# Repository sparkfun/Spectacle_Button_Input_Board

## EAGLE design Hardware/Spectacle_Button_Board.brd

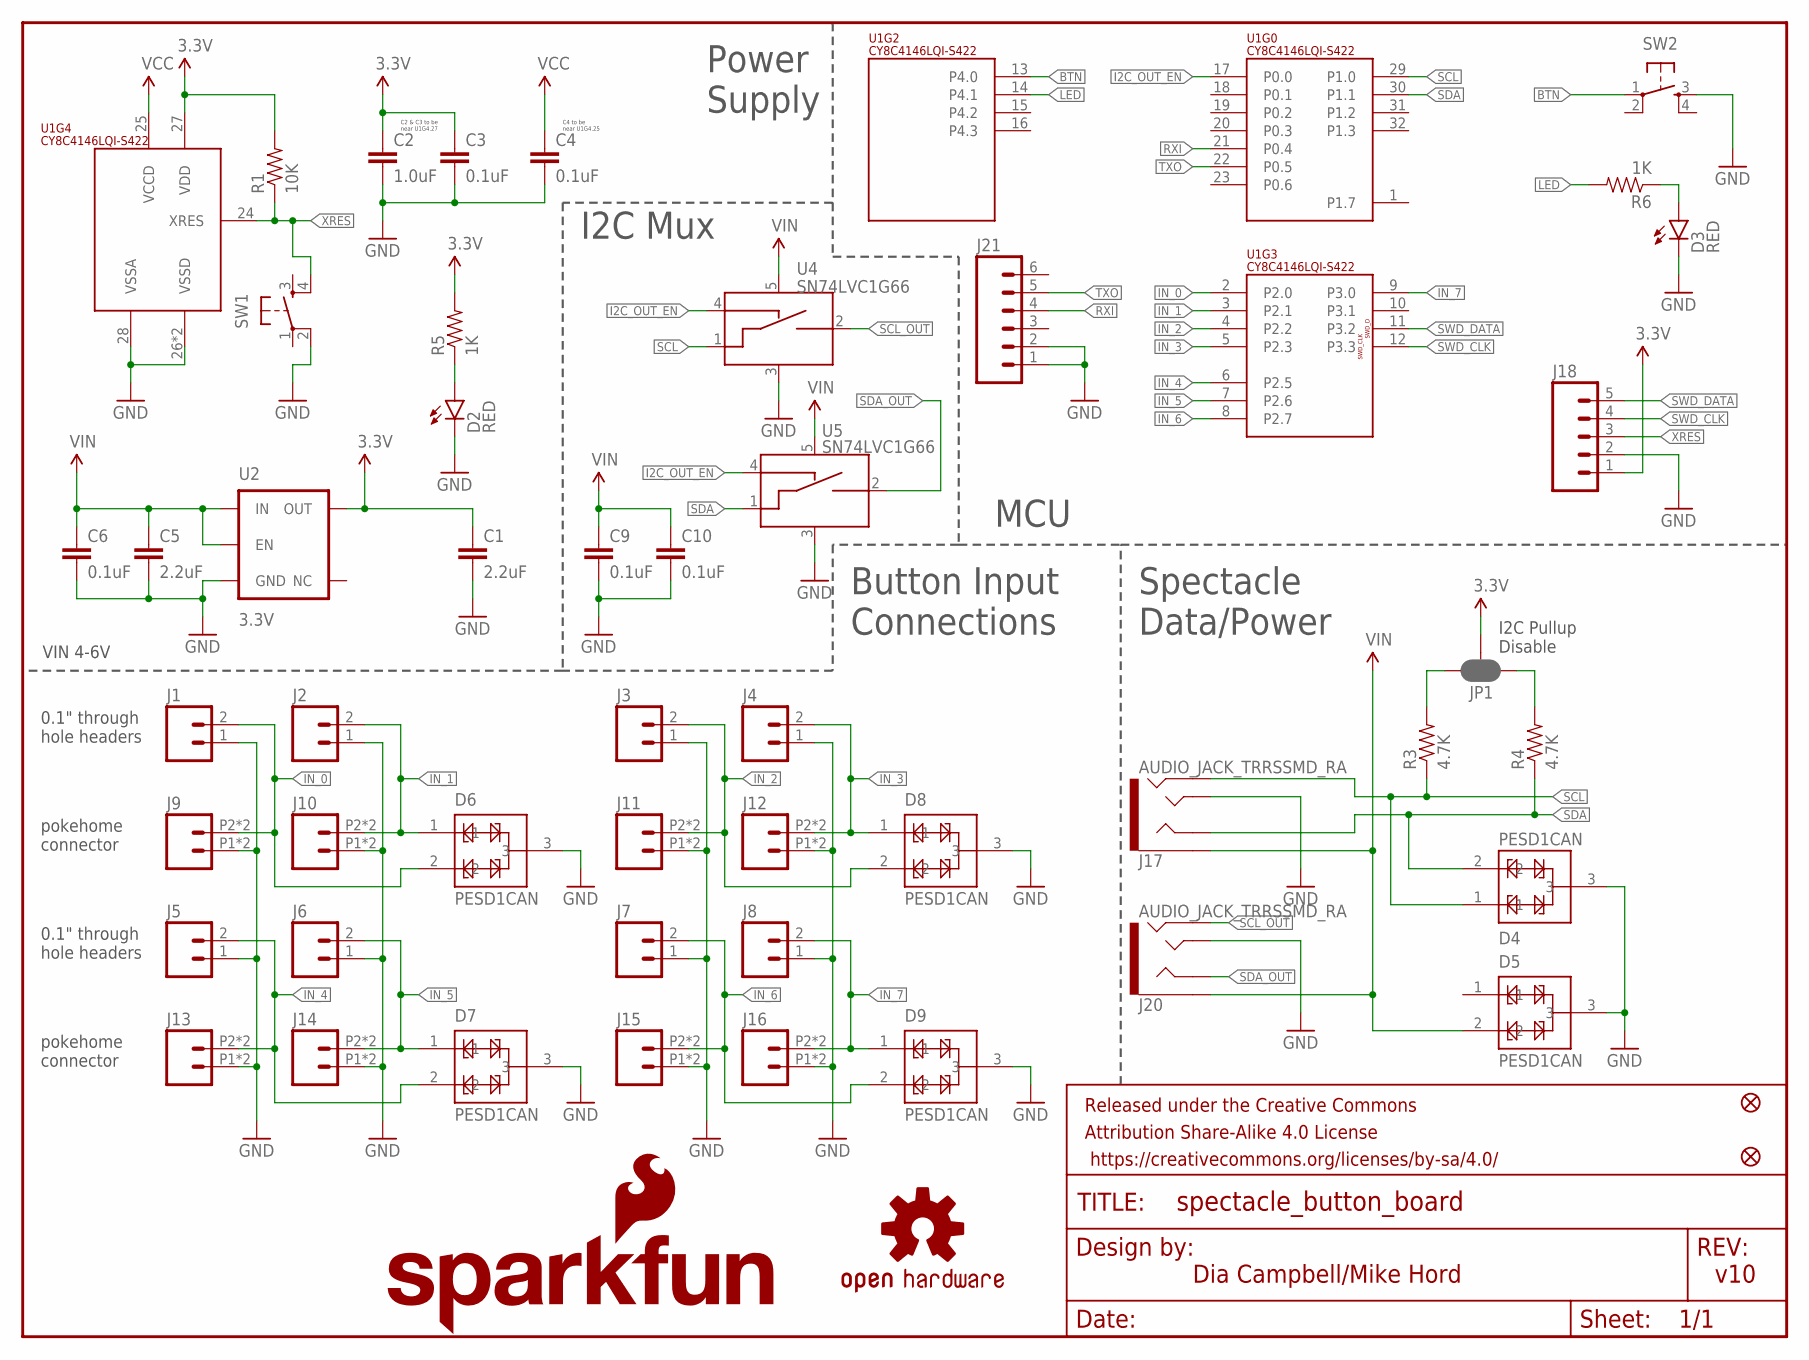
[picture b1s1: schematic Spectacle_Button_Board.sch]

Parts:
C1, C5: 2.2uF; 0603-CAP
C2: 1.0uF; 0402-CAP
C3, C4, C6, C9, C10: 0.1uF; 0402-CAP
D2, D3: RED; LED-0603
D4, D5, D6, D7, D8, D9: PESD1CAN; SOT23-3
FD1, FD2: FIDUCIALUFIDUCIAL; MICRO-FIDUCIAL
FRAME1: FRAME-LETTER; CREATIVE_COMMONS
J1, J2, J3, J4, J5, J6, J7, J8: M02PTH; 1X02
J9, J10, J11, J12, J13, J14, J15, J16: M02SMALL_POKEHOME; 1X02_POKEHOME
J17, J20: AUDIO_JACK_TRRSSMD_RA; AUDIO_JACK_3.5MM_TRRS_SMD_RA
J18: M05NO_SILK; 1X05_NO_SILK
J21: M06NO_SILK_NO_POP; 1X06_NO_SILK
JP1: JUMPER-PAD-3-NC_BY_PASTE; PAD-JUMPER-3-NC_BY_PASTE_YES_SILK_FULL_BOX
LOGO1: OSHW-LOGOM; OSHW-LOGO-M
LOGO2: SFE_LOGO_NAME_FLAME.1_INCH; SFE_LOGO_NAME_FLAME_.1
R1: 10K; 0603-RES
R3, R4: 4.7K; 0603-RES
R5, R6: 1K; 0603-RES
SW1, SW2: SWITCH_SPST_4_PINRECT; TACTILE_SWITCH_SMD_4.6X2.8MM
U1: CY8C4146LQI-S422; QFN-32
U2: 3.3V; SOT23-5
U4, U5: SN74LVC1G66; SOT23-5

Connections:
3.3V: C1.1, C2.1, C3.1, J18.1, JP1.2, R1.2, R5.2, U1.27 (VDD), U2.5 (OUT)
BTN: SW2.1, U1.13 (P4.0)
GND: C1.2, C2.2, C3.2, C4.2, C5.2, C6.2, C9.2, C10.2, D2.C, D3.C, D4.3, D5.3, D6.3, D7.3, D8.3, D9.3, J1.1, J2.1, J3.1, J4.1, J5.1, J6.1, J7.1, J8.1, J9.P1 (1), J9.P3 (1), J10.P1 (1), J10.P3 (1), J11.P1 (1), J11.P3 (1), J12.P1 (1), J12.P3 (1), J13.P1 (1), J13.P3 (1), J14.P1 (1), J14.P3 (1), J15.P1 (1), J15.P3 (1), J16.P1 (1), J16.P3 (1), J17.TIP, J18.2, J20.TIP, J21.1, J21.2, SW1.2, SW2.3, U1.26 (VSSD), U1.28 (VSSA), U1.EP (VSSD), U2.2 (GND), U4.3 (VSS), U5.3 (VSS)
I2C_OUT_EN: U1.17 (P0.0), U4.4 (CTRL_IN), U5.4 (CTRL_IN)
IN_0: D6.2, J1.2, J9.P2 (2), J9.P4 (2), U1.2 (P2.0)
IN_1: D6.1, J2.2, J10.P2 (2), J10.P4 (2), U1.3 (P2.1)
IN_2: D8.2, J3.2, J11.P2 (2), J11.P4 (2), U1.4 (P2.2)
IN_3: D8.1, J4.2, J12.P2 (2), J12.P4 (2), U1.5 (P2.3)
IN_4: D7.2, J5.2, J13.P2 (2), J13.P4 (2), U1.6 (P2.5)
IN_5: D7.1, J6.2, J14.P2 (2), J14.P4 (2), U1.7 (P2.6)
IN_6: D9.2, J7.2, J15.P2 (2), J15.P4 (2), U1.8 (P2.7)
IN_7: D9.1, J8.2, J16.P2 (2), J16.P4 (2), U1.9 (P3.0)
LED: R6.2, U1.14 (P4.1)
unnamed: JP1.3, R3.2
unnamed: D2.A, R5.1
unnamed: D3.A, R6.1
unnamed: JP1.1, R4.2
RXI: J21.4, U1.21 (P0.4)
SCL: D4.1, J17.RING2, R3.1, U1.29 (P1.0), U4.1 (A_IN)
SCL_OUT: J20.RING2, U4.2 (A_OUT)
SDA: D4.2, J17.RING1, R4.1, U1.30 (P1.1), U5.1 (A_IN)
SDA_OUT: J20.RING1, U5.2 (A_OUT)
SWD_CLK: J18.4, U1.12 (P3.3)
SWD_DATA: J18.5, U1.11 (P3.2)
TXO: J21.5, U1.22 (P0.5)
VCC: C4.1, U1.25 (VCCD)
VIN: C5.1, C6.1, C9.1, C10.1, D5.2, J17.EARTH, J20.EARTH, U2.1 (IN), U2.3 (EN), U4.5 (VCC), U5.5 (VCC)
XRES: J18.3, R1.1, SW1.4, U1.24 (XRES)

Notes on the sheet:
pokehome connector
0.1" through hole headers
C2 & C3 to be near U1G4.27
C4 to be near U1G4.25
Button Input Connections
Spectacle Data/Power
MCU
Power Supply
Dia Campbell/Mike Hord
v10
VIN 4-6V
I2C Mux
I2C Pullup Disable

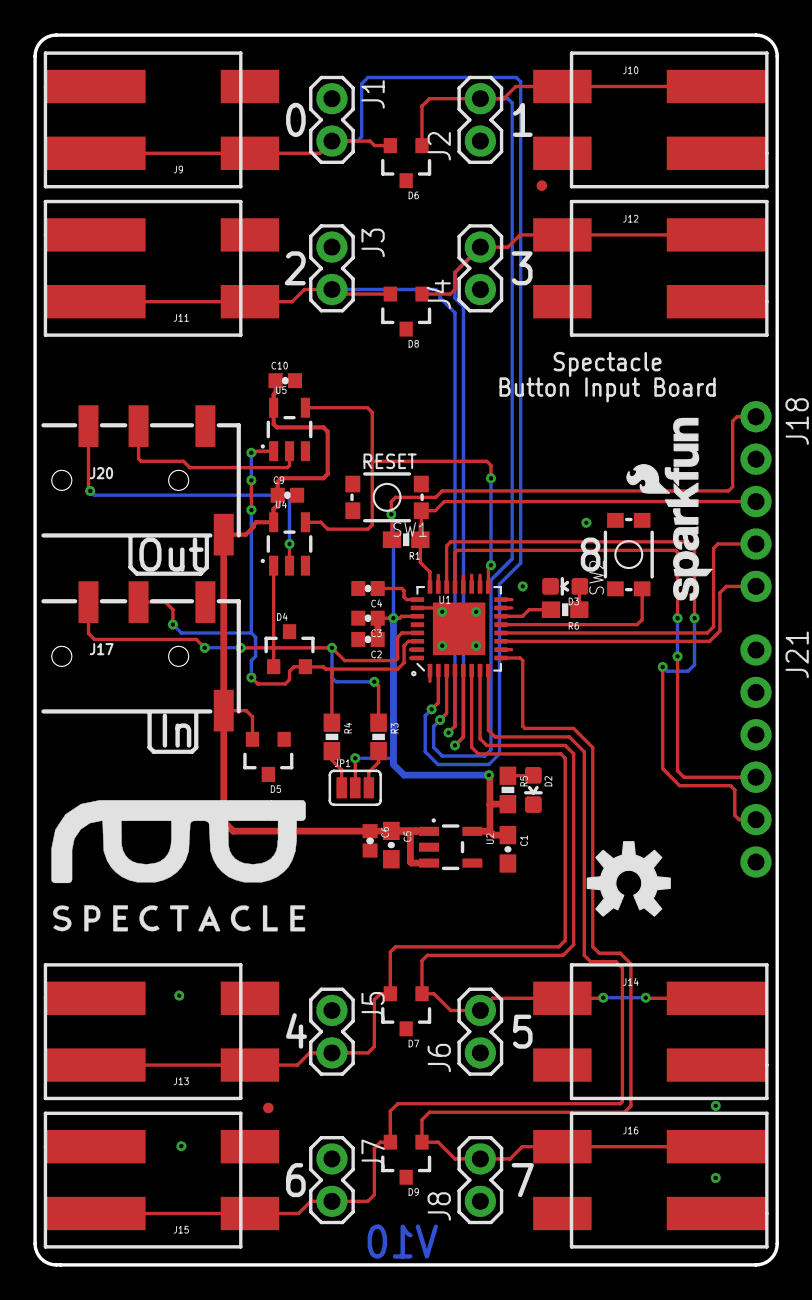
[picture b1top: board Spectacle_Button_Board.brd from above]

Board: 2 copper layers, 44.5 x 73.7 mm, 53 parts (0 on the bottom side), 28 nets.

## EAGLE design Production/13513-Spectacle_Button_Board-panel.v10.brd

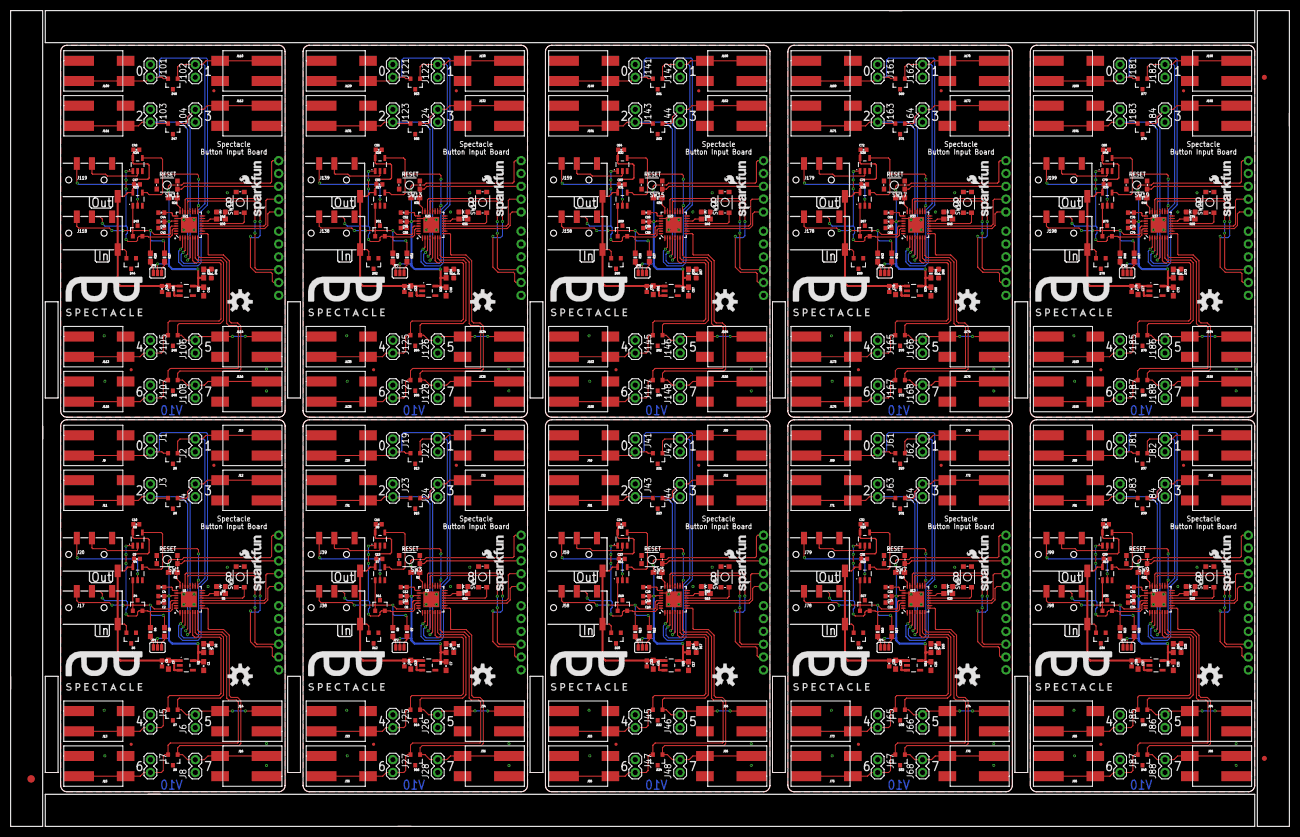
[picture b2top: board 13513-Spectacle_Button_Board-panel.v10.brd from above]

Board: 2 copper layers, 253.2 x 161.5 mm, 523 parts (0 on the bottom side), 280 nets.

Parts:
C1, C5, C7, C13, C17, C21, C25, C29, C33, C37, C41, C45, C49, C53, C57, C61, C65, C69, C73, C77: 2.2uF; 0603-CAP
C2, C8, C18, C26, C34, C42, C50, C58, C66, C74: 1.0uF; 0402-CAP
C3, C4, C6, C9, C10, C11, C12, C14, C15, C16, C19, C20, C22, C23, C24, C27, C28, C30, C31, C32, C35, C36, C38, C39, C40, C43, C44, C46, C47, C48, C51, C52, C54, C55, C56, C59, C60, C62, C63, C64, C67, C68, C70, C71, C72, C75, C76, C78, C79, C80: 0.1uF; 0402-CAP
D1, D2, D3, D10, D17, D18, D25, D26, D33, D34, D41, D42, D49, D50, D57, D58, D65, D66, D73, D74: RED; LED-0603
D4, D5, D6, D7, D8, D9, D11, D12, D13, D14, D15, D16, D19, D20, D21, D22, D23, D24, D27, D28, D29, D30, D31, D32, D35, D36, D37, D38, D39, D40, D43, D44, D45, D46, D47, D48, D51, D52, D53, D54, D55, D56, D59, D60, D61, D62, D63, D64, D67, D68, D69, D70, D71, D72, D75, D76, D77, D78, D79, D80: PESD1CAN; SOT23-3
E$1: FIDUCIAL-1.5X3
E$7, E$8: FIDUCIAL-1X2
FD1, FD2, FD3, FD4, FD5, FD6, FD7, FD8, FD9, FD10, FD11, FD12, FD13, FD14, FD15, FD16, FD17, FD18, FD19, FD20: FIDUCIALUFIDUCIAL; MICRO-FIDUCIAL
J1, J2, J3, J4, J5, J6, J7, J8, J19, J22, J23, J24, J25, J26, J27, J28, J41, J42, J43, J44, J45, J46, J47, J48, J61, J62, J63, J64, J65, J66, J67, J68, J81, J82, J83, J84, J85, J86, J87, J88, J101, J102, J103, J104, J105, J106, J107, J108, J121, J122, J123, J124, J125, J126, J127, J128, J141, J142, J143, J144, J145, J146, J147, J148, J161, J162, J163, J164, J165, J166, J167, J168, J181, J182, J183, J184, J185, J186, J187, J188: 1X02
J9, J10, J11, J12, J13, J14, J15, J16, J29, J30, J31, J32, J33, J34, J35, J36, J49, J50, J51, J52, J53, J54, J55, J56, J69, J70, J71, J72, J73, J74, J75, J76, J89, J90, J91, J92, J93, J94, J95, J96, J109, J110, J111, J112, J113, J114, J115, J116, J129, J130, J131, J132, J133, J134, J135, J136, J149, J150, J151, J152, J153, J154, J155, J156, J169, J170, J171, J172, J173, J174, J175, J176, J189, J190, J191, J192, J193, J194, J195, J196: 1X02_POKEHOME
J17, J20, J38, J39, J58, J59, J78, J79, J98, J99, J118, J119, J138, J139, J158, J159, J178, J179, J198, J199: AUDIO_JACK_TRRSSMD_RA; AUDIO_JACK_3.5MM_TRRS_SMD_RA
J18, J37, J57, J77, J97, J117, J137, J157, J177, J197: 1X05_NO_SILK
J21, J40, J60, J80, J100, J120, J140, J160, J180, J200: 1X06_NO_SILK
JP1, JP2, JP3, JP4, JP5, JP6, JP7, JP8, JP9, JP10: JUMPER-PAD-3-NC_BY_PASTE; PAD-JUMPER-3-NC_BY_PASTE_YES_SILK_FULL_BOX
LOGO1, LOGO3, LOGO5, LOGO7, LOGO9, LOGO11, LOGO13, LOGO15, LOGO17, LOGO19: OSHW-LOGOM; OSHW-LOGO-M
LOGO2, LOGO4, LOGO6, LOGO8, LOGO10, LOGO12, LOGO14, LOGO16, LOGO18, LOGO20: SFE_LOGO_NAME_FLAME.1_INCH; SFE_LOGO_NAME_FLAME_.1
R1, R2, R11, R16, R21, R26, R31, R36, R41, R46: 10K; 0603-RES
R3, R4, R7, R8, R12, R13, R17, R18, R22, R23, R27, R28, R32, R33, R37, R38, R42, R43, R47, R48: 4.7K; 0603-RES
R5, R6, R9, R10, R14, R15, R19, R20, R24, R25, R29, R30, R34, R35, R39, R40, R44, R45, R49, R50: 1K; 0603-RES
SW1, SW2, SW3, SW4, SW5, SW6, SW7, SW8, SW9, SW10, SW11, SW12, SW13, SW14, SW15, SW16, SW17, SW18, SW19, SW20: TACTILE_SWITCH_SMD_4.6X2.8MM
U1, U3, U9, U13, U17, U21, U25, U29, U33, U37: CY8C4146LQI-S422; QFN-32
U2, U6, U10, U14, U18, U22, U26, U30, U34, U38: 3.3V; SOT23-5
U4, U5, U7, U8, U11, U12, U15, U16, U19, U20, U23, U24, U27, U28, U31, U32, U35, U36, U39, U40: SN74LVC1G66; SOT23-5

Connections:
3.3V: C1.1, C2.1, C3.1, J18.1, JP1.2, R1.2, R5.2, U1.27, U2.5
3.3V1: C7.1, C8.1, C11.1, J37.1, JP2.2, R2.2, R9.2, U3.27, U6.5
3.3V2: C17.1, C18.1, C19.1, J57.1, JP3.2, R11.2, R14.2, U9.27, U10.5
3.3V3: C25.1, C26.1, C27.1, J77.1, JP4.2, R16.2, R19.2, U13.27, U14.5
3.3V4: C33.1, C34.1, C35.1, J97.1, JP5.2, R21.2, R24.2, U17.27, U18.5
3.3V5: C41.1, C42.1, C43.1, J117.1, JP6.2, R26.2, R29.2, U21.27, U22.5
3.3V6: C49.1, C50.1, C51.1, J137.1, JP7.2, R31.2, R34.2, U25.27, U26.5
3.3V7: C57.1, C58.1, C59.1, J157.1, JP8.2, R36.2, R39.2, U29.27, U30.5
3.3V8: C65.1, C66.1, C67.1, J177.1, JP9.2, R41.2, R44.2, U33.27, U34.5
3.3V9: C73.1, C74.1, C75.1, J197.1, JP10.2, R46.2, R49.2, U37.27, U38.5
BTN: SW2.1, U1.13
BTN1: SW4.1, U3.13
BTN2: SW6.1, U9.13
BTN3: SW8.1, U13.13
BTN4: SW10.1, U17.13
BTN5: SW12.1, U21.13
BTN6: SW14.1, U25.13
BTN7: SW16.1, U29.13
BTN8: SW18.1, U33.13
BTN9: SW20.1, U37.13
GND: C1.2, C2.2, C3.2, C4.2, C5.2, C6.2, C9.2, C10.2, D2.C, D3.C, D4.3, D5.3, D6.3, D7.3, D8.3, D9.3, J1.1, J2.1, J3.1, J4.1, J5.1, J6.1, J7.1, J8.1, J9.P1, J9.P3, J10.P1, J10.P3, J11.P1, J11.P3, J12.P1, J12.P3, J13.P1, J13.P3, J14.P1, J14.P3, J15.P1, J15.P3, J16.P1, J16.P3, J17.TIP, J18.2, J20.TIP, J21.1, J21.2, SW1.2, SW2.3, U1.26, U1.28, U1.EP, U2.2, U4.3, U5.3
GND1: C7.2, C8.2, C11.2, C12.2, C13.2, C14.2, C15.2, C16.2, D1.C, D10.C, D11.3, D12.3, D13.3, D14.3, D15.3, D16.3, J19.1, J22.1, J23.1, J24.1, J25.1, J26.1, J27.1, J28.1, J29.P1, J29.P3, J30.P1, J30.P3, J31.P1, J31.P3, J32.P1, J32.P3, J33.P1, J33.P3, J34.P1, J34.P3, J35.P1, J35.P3, J36.P1, J36.P3, J37.2, J38.TIP, J39.TIP, J40.1, J40.2, SW3.2, SW4.3, U3.26, U3.28, U3.EP, U6.2, U7.3, U8.3
GND2: C17.2, C18.2, C19.2, C20.2, C21.2, C22.2, C23.2, C24.2, D17.C, D18.C, D19.3, D20.3, D21.3, D22.3, D23.3, D24.3, J41.1, J42.1, J43.1, J44.1, J45.1, J46.1, J47.1, J48.1, J49.P1, J49.P3, J50.P1, J50.P3, J51.P1, J51.P3, J52.P1, J52.P3, J53.P1, J53.P3, J54.P1, J54.P3, J55.P1, J55.P3, J56.P1, J56.P3, J57.2, J58.TIP, J59.TIP, J60.1, J60.2, SW5.2, SW6.3, U9.26, U9.28, U9.EP, U10.2, U11.3, U12.3
GND3: C25.2, C26.2, C27.2, C28.2, C29.2, C30.2, C31.2, C32.2, D25.C, D26.C, D27.3, D28.3, D29.3, D30.3, D31.3, D32.3, J61.1, J62.1, J63.1, J64.1, J65.1, J66.1, J67.1, J68.1, J69.P1, J69.P3, J70.P1, J70.P3, J71.P1, J71.P3, J72.P1, J72.P3, J73.P1, J73.P3, J74.P1, J74.P3, J75.P1, J75.P3, J76.P1, J76.P3, J77.2, J78.TIP, J79.TIP, J80.1, J80.2, SW7.2, SW8.3, U13.26, U13.28, U13.EP, U14.2, U15.3, U16.3
GND4: C33.2, C34.2, C35.2, C36.2, C37.2, C38.2, C39.2, C40.2, D33.C, D34.C, D35.3, D36.3, D37.3, D38.3, D39.3, D40.3, J81.1, J82.1, J83.1, J84.1, J85.1, J86.1, J87.1, J88.1, J89.P1, J89.P3, J90.P1, J90.P3, J91.P1, J91.P3, J92.P1, J92.P3, J93.P1, J93.P3, J94.P1, J94.P3, J95.P1, J95.P3, J96.P1, J96.P3, J97.2, J98.TIP, J99.TIP, J100.1, J100.2, SW9.2, SW10.3, U17.26, U17.28, U17.EP, U18.2, U19.3, U20.3
GND5: C41.2, C42.2, C43.2, C44.2, C45.2, C46.2, C47.2, C48.2, D41.C, D42.C, D43.3, D44.3, D45.3, D46.3, D47.3, D48.3, J101.1, J102.1, J103.1, J104.1, J105.1, J106.1, J107.1, J108.1, J109.P1, J109.P3, J110.P1, J110.P3, J111.P1, J111.P3, J112.P1, J112.P3, J113.P1, J113.P3, J114.P1, J114.P3, J115.P1, J115.P3, J116.P1, J116.P3, J117.2, J118.TIP, J119.TIP, J120.1, J120.2, SW11.2, SW12.3, U21.26, U21.28, U21.EP, U22.2, U23.3, U24.3
GND6: C49.2, C50.2, C51.2, C52.2, C53.2, C54.2, C55.2, C56.2, D49.C, D50.C, D51.3, D52.3, D53.3, D54.3, D55.3, D56.3, J121.1, J122.1, J123.1, J124.1, J125.1, J126.1, J127.1, J128.1, J129.P1, J129.P3, J130.P1, J130.P3, J131.P1, J131.P3, J132.P1, J132.P3, J133.P1, J133.P3, J134.P1, J134.P3, J135.P1, J135.P3, J136.P1, J136.P3, J137.2, J138.TIP, J139.TIP, J140.1, J140.2, SW13.2, SW14.3, U25.26, U25.28, U25.EP, U26.2, U27.3, U28.3
GND7: C57.2, C58.2, C59.2, C60.2, C61.2, C62.2, C63.2, C64.2, D57.C, D58.C, D59.3, D60.3, D61.3, D62.3, D63.3, D64.3, J141.1, J142.1, J143.1, J144.1, J145.1, J146.1, J147.1, J148.1, J149.P1, J149.P3, J150.P1, J150.P3, J151.P1, J151.P3, J152.P1, J152.P3, J153.P1, J153.P3, J154.P1, J154.P3, J155.P1, J155.P3, J156.P1, J156.P3, J157.2, J158.TIP, J159.TIP, J160.1, J160.2, SW15.2, SW16.3, U29.26, U29.28, U29.EP, U30.2, U31.3, U32.3
GND8: C65.2, C66.2, C67.2, C68.2, C69.2, C70.2, C71.2, C72.2, D65.C, D66.C, D67.3, D68.3, D69.3, D70.3, D71.3, D72.3, J161.1, J162.1, J163.1, J164.1, J165.1, J166.1, J167.1, J168.1, J169.P1, J169.P3, J170.P1, J170.P3, J171.P1, J171.P3, J172.P1, J172.P3, J173.P1, J173.P3, J174.P1, J174.P3, J175.P1, J175.P3, J176.P1, J176.P3, J177.2, J178.TIP, J179.TIP, J180.1, J180.2, SW17.2, SW18.3, U33.26, U33.28, U33.EP, U34.2, U35.3, U36.3
GND9: C73.2, C74.2, C75.2, C76.2, C77.2, C78.2, C79.2, C80.2, D73.C, D74.C, D75.3, D76.3, D77.3, D78.3, D79.3, D80.3, J181.1, J182.1, J183.1, J184.1, J185.1, J186.1, J187.1, J188.1, J189.P1, J189.P3, J190.P1, J190.P3, J191.P1, J191.P3, J192.P1, J192.P3, J193.P1, J193.P3, J194.P1, J194.P3, J195.P1, J195.P3, J196.P1, J196.P3, J197.2, J198.TIP, J199.TIP, J200.1, J200.2, SW19.2, SW20.3, U37.26, U37.28, U37.EP, U38.2, U39.3, U40.3
I2C_OUT_EN: U1.17, U4.4, U5.4
I2C_OUT_EN1: U3.17, U7.4, U8.4
I2C_OUT_EN2: U9.17, U11.4, U12.4
I2C_OUT_EN3: U13.17, U15.4, U16.4
I2C_OUT_EN4: U17.17, U19.4, U20.4
I2C_OUT_EN5: U21.17, U23.4, U24.4
I2C_OUT_EN6: U25.17, U27.4, U28.4
I2C_OUT_EN7: U29.17, U31.4, U32.4
I2C_OUT_EN8: U33.17, U35.4, U36.4
I2C_OUT_EN9: U37.17, U39.4, U40.4
IN_0: D6.2, J1.2, J9.P2, J9.P4, U1.2
IN_1: D6.1, J2.2, J10.P2, J10.P4, U1.3
IN_2: D8.2, J3.2, J11.P2, J11.P4, U1.4
IN_3: D8.1, J4.2, J12.P2, J12.P4, U1.5
IN_4: D7.2, J5.2, J13.P2, J13.P4, U1.6
IN_5: D7.1, J6.2, J14.P2, J14.P4, U1.7
IN_6: D9.2, J7.2, J15.P2, J15.P4, U1.8
IN_7: D9.1, J8.2, J16.P2, J16.P4, U1.9
IN_8: D13.2, J19.2, J29.P2, J29.P4, U3.2
IN_9: D13.1, J22.2, J30.P2, J30.P4, U3.3
IN_10: D15.2, J23.2, J31.P2, J31.P4, U3.4
IN_11: D15.1, J24.2, J32.P2, J32.P4, U3.5
IN_12: D16.1, J28.2, J36.P2, J36.P4, U3.9
IN_13: D14.1, J26.2, J34.P2, J34.P4, U3.7
IN_14: D14.2, J25.2, J33.P2, J33.P4, U3.6
IN_15: D16.2, J27.2, J35.P2, J35.P4, U3.8
IN_16: D21.2, J41.2, J49.P2, J49.P4, U9.2
IN_17: D21.1, J42.2, J50.P2, J50.P4, U9.3
IN_18: D23.2, J43.2, J51.P2, J51.P4, U9.4
IN_19: D23.1, J44.2, J52.P2, J52.P4, U9.5
IN_20: D24.1, J48.2, J56.P2, J56.P4, U9.9
IN_21: D22.1, J46.2, J54.P2, J54.P4, U9.7
IN_22: D22.2, J45.2, J53.P2, J53.P4, U9.6
IN_23: D24.2, J47.2, J55.P2, J55.P4, U9.8
IN_24: D29.2, J61.2, J69.P2, J69.P4, U13.2
IN_25: D29.1, J62.2, J70.P2, J70.P4, U13.3
IN_26: D31.2, J63.2, J71.P2, J71.P4, U13.4
IN_27: D31.1, J64.2, J72.P2, J72.P4, U13.5
IN_28: D32.1, J68.2, J76.P2, J76.P4, U13.9
IN_29: D30.1, J66.2, J74.P2, J74.P4, U13.7
IN_30: D30.2, J65.2, J73.P2, J73.P4, U13.6
IN_31: D32.2, J67.2, J75.P2, J75.P4, U13.8
IN_32: D37.2, J81.2, J89.P2, J89.P4, U17.2
IN_33: D37.1, J82.2, J90.P2, J90.P4, U17.3
IN_34: D39.2, J83.2, J91.P2, J91.P4, U17.4
IN_35: D39.1, J84.2, J92.P2, J92.P4, U17.5
IN_36: D40.1, J88.2, J96.P2, J96.P4, U17.9
IN_37: D38.1, J86.2, J94.P2, J94.P4, U17.7
IN_38: D38.2, J85.2, J93.P2, J93.P4, U17.6
IN_39: D40.2, J87.2, J95.P2, J95.P4, U17.8
IN_40: D45.2, J101.2, J109.P2, J109.P4, U21.2
IN_41: D45.1, J102.2, J110.P2, J110.P4, U21.3
IN_42: D47.2, J103.2, J111.P2, J111.P4, U21.4
IN_43: D47.1, J104.2, J112.P2, J112.P4, U21.5
IN_44: D48.1, J108.2, J116.P2, J116.P4, U21.9
IN_45: D46.1, J106.2, J114.P2, J114.P4, U21.7
IN_46: D46.2, J105.2, J113.P2, J113.P4, U21.6
IN_47: D48.2, J107.2, J115.P2, J115.P4, U21.8
IN_48: D53.2, J121.2, J129.P2, J129.P4, U25.2
IN_49: D53.1, J122.2, J130.P2, J130.P4, U25.3
IN_50: D55.2, J123.2, J131.P2, J131.P4, U25.4
IN_51: D55.1, J124.2, J132.P2, J132.P4, U25.5
IN_52: D56.1, J128.2, J136.P2, J136.P4, U25.9
IN_53: D54.1, J126.2, J134.P2, J134.P4, U25.7
IN_54: D54.2, J125.2, J133.P2, J133.P4, U25.6
IN_55: D56.2, J127.2, J135.P2, J135.P4, U25.8
IN_56: D61.2, J141.2, J149.P2, J149.P4, U29.2
IN_57: D61.1, J142.2, J150.P2, J150.P4, U29.3
IN_58: D63.2, J143.2, J151.P2, J151.P4, U29.4
IN_59: D63.1, J144.2, J152.P2, J152.P4, U29.5
IN_60: D64.1, J148.2, J156.P2, J156.P4, U29.9
IN_61: D62.1, J146.2, J154.P2, J154.P4, U29.7
IN_62: D62.2, J145.2, J153.P2, J153.P4, U29.6
IN_63: D64.2, J147.2, J155.P2, J155.P4, U29.8
IN_64: D69.2, J161.2, J169.P2, J169.P4, U33.2
IN_65: D69.1, J162.2, J170.P2, J170.P4, U33.3
IN_66: D71.2, J163.2, J171.P2, J171.P4, U33.4
IN_67: D71.1, J164.2, J172.P2, J172.P4, U33.5
IN_68: D72.1, J168.2, J176.P2, J176.P4, U33.9
IN_69: D70.1, J166.2, J174.P2, J174.P4, U33.7
IN_70: D70.2, J165.2, J173.P2, J173.P4, U33.6
IN_71: D72.2, J167.2, J175.P2, J175.P4, U33.8
IN_72: D77.2, J181.2, J189.P2, J189.P4, U37.2
IN_73: D77.1, J182.2, J190.P2, J190.P4, U37.3
IN_74: D79.2, J183.2, J191.P2, J191.P4, U37.4
IN_75: D79.1, J184.2, J192.P2, J192.P4, U37.5
IN_76: D80.1, J188.2, J196.P2, J196.P4, U37.9
IN_77: D78.1, J186.2, J194.P2, J194.P4, U37.7
IN_78: D78.2, J185.2, J193.P2, J193.P4, U37.6
IN_79: D80.2, J187.2, J195.P2, J195.P4, U37.8
LED: R6.2, U1.14
LED1: R10.2, U3.14
LED2: R15.2, U9.14
LED3: R20.2, U13.14
LED4: R25.2, U17.14
LED5: R30.2, U21.14
LED6: R35.2, U25.14
LED7: R40.2, U29.14
LED8: R45.2, U33.14
LED9: R50.2, U37.14
unnamed: JP1.3, R3.2
unnamed: JP2.3, R7.2
unnamed: D2.A, R5.1
unnamed: D3.A, R6.1
unnamed: JP1.1, R4.2
unnamed: JP2.1, R8.2
unnamed: D1.A, R9.1
unnamed: D10.A, R10.1
unnamed: JP3.3, R12.2
unnamed: JP3.1, R13.2
unnamed: D17.A, R14.1
unnamed: D18.A, R15.1
unnamed: JP4.3, R17.2
unnamed: JP4.1, R18.2
unnamed: D25.A, R19.1
unnamed: D26.A, R20.1
unnamed: JP5.3, R22.2
unnamed: JP5.1, R23.2
unnamed: D33.A, R24.1
unnamed: D34.A, R25.1
unnamed: JP6.3, R27.2
unnamed: JP6.1, R28.2
unnamed: D41.A, R29.1
unnamed: D42.A, R30.1
unnamed: JP7.3, R32.2
unnamed: JP7.1, R33.2
unnamed: D49.A, R34.1
unnamed: D50.A, R35.1
unnamed: JP8.3, R37.2
unnamed: JP8.1, R38.2
unnamed: D57.A, R39.1
unnamed: D58.A, R40.1
unnamed: JP9.3, R42.2
unnamed: JP9.1, R43.2
unnamed: D65.A, R44.1
unnamed: D66.A, R45.1
unnamed: JP10.3, R47.2
unnamed: JP10.1, R48.2
unnamed: D73.A, R49.1
unnamed: D74.A, R50.1
RXI: J21.4, U1.21
RXI1: J40.4, U3.21
RXI2: J60.4, U9.21
RXI3: J80.4, U13.21
RXI4: J100.4, U17.21
RXI5: J120.4, U21.21
RXI6: J140.4, U25.21
RXI7: J160.4, U29.21
RXI8: J180.4, U33.21
RXI9: J200.4, U37.21
SCL: D4.1, J17.RING2, R3.1, U1.29, U4.1
SCL1: D11.1, J38.RING2, R7.1, U3.29, U7.1
SCL2: D19.1, J58.RING2, R12.1, U9.29, U11.1
SCL3: D27.1, J78.RING2, R17.1, U13.29, U15.1
SCL4: D35.1, J98.RING2, R22.1, U17.29, U19.1
SCL5: D43.1, J118.RING2, R27.1, U21.29, U23.1
SCL6: D51.1, J138.RING2, R32.1, U25.29, U27.1
SCL7: D59.1, J158.RING2, R37.1, U29.29, U31.1
SCL8: D67.1, J178.RING2, R42.1, U33.29, U35.1
SCL9: D75.1, J198.RING2, R47.1, U37.29, U39.1
SCL_OUT: J20.RING2, U4.2
SCL_OUT1: J39.RING2, U7.2
SCL_OUT2: J59.RING2, U11.2
SCL_OUT3: J79.RING2, U15.2
SCL_OUT4: J99.RING2, U19.2
SCL_OUT5: J119.RING2, U23.2
SCL_OUT6: J139.RING2, U27.2
SCL_OUT7: J159.RING2, U31.2
SCL_OUT8: J179.RING2, U35.2
SCL_OUT9: J199.RING2, U39.2
SDA: D4.2, J17.RING1, R4.1, U1.30, U5.1
SDA1: D11.2, J38.RING1, R8.1, U3.30, U8.1
SDA2: D19.2, J58.RING1, R13.1, U9.30, U12.1
SDA3: D27.2, J78.RING1, R18.1, U13.30, U16.1
SDA4: D35.2, J98.RING1, R23.1, U17.30, U20.1
SDA5: D43.2, J118.RING1, R28.1, U21.30, U24.1
SDA6: D51.2, J138.RING1, R33.1, U25.30, U28.1
SDA7: D59.2, J158.RING1, R38.1, U29.30, U32.1
SDA8: D67.2, J178.RING1, R43.1, U33.30, U36.1
SDA9: D75.2, J198.RING1, R48.1, U37.30, U40.1
SDA_OUT: J20.RING1, U5.2
SDA_OUT1: J39.RING1, U8.2
SDA_OUT2: J59.RING1, U12.2
SDA_OUT3: J79.RING1, U16.2
SDA_OUT4: J99.RING1, U20.2
SDA_OUT5: J119.RING1, U24.2
SDA_OUT6: J139.RING1, U28.2
SDA_OUT7: J159.RING1, U32.2
SDA_OUT8: J179.RING1, U36.2
SDA_OUT9: J199.RING1, U40.2
SWD_CLK: J18.4, U1.12
SWD_CLK1: J37.4, U3.12
SWD_CLK2: J57.4, U9.12
SWD_CLK3: J77.4, U13.12
SWD_CLK4: J97.4, U17.12
SWD_CLK5: J117.4, U21.12
SWD_CLK6: J137.4, U25.12
SWD_CLK7: J157.4, U29.12
SWD_CLK8: J177.4, U33.12
SWD_CLK9: J197.4, U37.12
SWD_DATA: J18.5, U1.11
SWD_DATA1: J37.5, U3.11
SWD_DATA2: J57.5, U9.11
SWD_DATA3: J77.5, U13.11
SWD_DATA4: J97.5, U17.11
SWD_DATA5: J117.5, U21.11
SWD_DATA6: J137.5, U25.11
SWD_DATA7: J157.5, U29.11
SWD_DATA8: J177.5, U33.11
SWD_DATA9: J197.5, U37.11
TXO: J21.5, U1.22
TXO1: J40.5, U3.22
TXO2: J60.5, U9.22
TXO3: J80.5, U13.22
TXO4: J100.5, U17.22
TXO5: J120.5, U21.22
TXO6: J140.5, U25.22
TXO7: J160.5, U29.22
TXO8: J180.5, U33.22
TXO9: J200.5, U37.22
VCC: C4.1, U1.25
VCC1: C12.1, U3.25
VCC2: C20.1, U9.25
VCC3: C28.1, U13.25
VCC4: C36.1, U17.25
VCC5: C44.1, U21.25
VCC6: C52.1, U25.25
VCC7: C60.1, U29.25
VCC8: C68.1, U33.25
VCC9: C76.1, U37.25
VIN: C5.1, C6.1, C9.1, C10.1, D5.2, J17.EARTH, J20.EARTH, U2.1, U2.3, U4.5, U5.5
VIN1: C13.1, C14.1, C15.1, C16.1, D12.2, J38.EARTH, J39.EARTH, U6.1, U6.3, U7.5, U8.5
VIN2: C21.1, C22.1, C23.1, C24.1, D20.2, J58.EARTH, J59.EARTH, U10.1, U10.3, U11.5, U12.5
VIN3: C29.1, C30.1, C31.1, C32.1, D28.2, J78.EARTH, J79.EARTH, U14.1, U14.3, U15.5, U16.5
VIN4: C37.1, C38.1, C39.1, C40.1, D36.2, J98.EARTH, J99.EARTH, U18.1, U18.3, U19.5, U20.5
VIN5: C45.1, C46.1, C47.1, C48.1, D44.2, J118.EARTH, J119.EARTH, U22.1, U22.3, U23.5, U24.5
VIN6: C53.1, C54.1, C55.1, C56.1, D52.2, J138.EARTH, J139.EARTH, U26.1, U26.3, U27.5, U28.5
VIN7: C61.1, C62.1, C63.1, C64.1, D60.2, J158.EARTH, J159.EARTH, U30.1, U30.3, U31.5, U32.5
VIN8: C69.1, C70.1, C71.1, C72.1, D68.2, J178.EARTH, J179.EARTH, U34.1, U34.3, U35.5, U36.5
VIN9: C77.1, C78.1, C79.1, C80.1, D76.2, J198.EARTH, J199.EARTH, U38.1, U38.3, U39.5, U40.5
XRES: J18.3, R1.1, SW1.4, U1.24
XRES1: J37.3, R2.1, SW3.4, U3.24
XRES2: J57.3, R11.1, SW5.4, U9.24
XRES3: J77.3, R16.1, SW7.4, U13.24
XRES4: J97.3, R21.1, SW9.4, U17.24
XRES5: J117.3, R26.1, SW11.4, U21.24
XRES6: J137.3, R31.1, SW13.4, U25.24
XRES7: J157.3, R36.1, SW15.4, U29.24
XRES8: J177.3, R41.1, SW17.4, U33.24
XRES9: J197.3, R46.1, SW19.4, U37.24

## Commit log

2016-06-13 Make some chgs (see full msg) - Add TVS diodes to all button and data/power lines - Partition schematic according to function - Change power/data connector to TRRS
2016-06-13 Fix TX and RX net names
2016-06-13 Adjust to 3.3V
2016-06-14 Remove diode from serial port to VIN
2016-08-26 Changed to pokehome connectors
2016-09-06 Added second trrs connector
2016-09-08 partially routed
2016-09-08 routed second half
    pushing a lot of small changes because Eagle has been crashing and I
    don't want to lose progress
2016-09-09 first draft routing
2016-09-09 added silk and dimensions
2016-09-09 Added spectacle logos
2016-09-13 Final for review
2016-09-13 added staking vias, straightened headers
2016-09-13 Quick schematic changes, ready for QC review
2016-09-13 Changed text on connectors
2016-09-15 Checklist edits
2016-09-15 Removed tabs on ground pad
2016-10-10 Added circuitry for downstream power control
2016-10-13 Revised for downstream power circuit
2016-10-13 Fixed VIN and VOUT lines
2016-10-18 added input and output silk
2016-10-26 Added I2C Mux hardware
2016-11-03 Added I2C switching circuitry
2016-11-07 Fixes from review and checklist
2016-11-08 Chg VREG to APK2112
2016-11-08 Change pullups to 4.7k
2016-11-08 Adjusted silk positions per QC double check review
2016-12-20 Initial firmware commit. All functionality passes first-level test.
2017-01-24 Clean up in preparation for release - Removed some debugging features that were unused - Added header information to code files
2017-01-25 Reduced configuration data size
2017-02-01 Version number update!
    v10
2017-02-09 added v to version number
2017-02-10 rounded corners
2017-02-14 Edges rounded
2017-02-15 panel
2017-04-04 Code commit for production
2017-04-05 Change UART speed to 9600

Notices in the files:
parts and their libraries:
SparkFun-Aesthetics: Licensing: Creative Commons ShareAlike 4.0 International - https://creativecommons.org/licenses/by-sa/4.0
SparkFun-Aesthetics: Released under the Creative Commons Attribution Share-Alike 4.0 License
SparkFun-Aesthetics: https://creativecommons.org/licenses/by-sa/4.0
